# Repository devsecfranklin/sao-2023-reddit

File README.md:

# Shitty Add-On of Reddit avatar for DEFCON 2023

```sh
 ____  _____      _    ____    _  ___     ____ ____  
|  _ \| ____|_   / \  |  _ \ _/ |/ _ \ _ / ___| ___| 
| | | |  _| (_) / _ \ | | | (_) | | | (_) |   |___ \ 
| |_| | |___ _ / ___ \| |_| |_| | |_| |_| |___ ___) |
|____/|_____(_)_/   \_\____/(_)_|\___/(_)\____|____/ 
                                                     
```

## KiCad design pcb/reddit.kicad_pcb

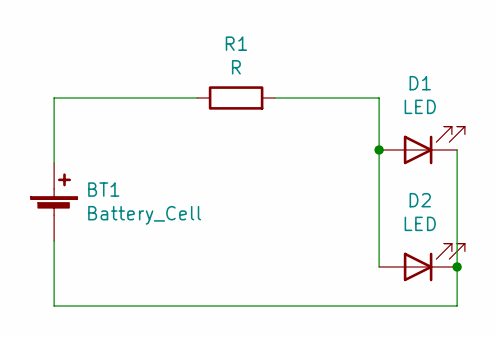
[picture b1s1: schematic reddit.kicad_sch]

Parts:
BT1: Battery_Cell; BatteryHolder_Keystone_3002_1x2032
D1, D2: LED; LED_PLCC-2_Reverse-Mount
R1: R; R_0805_2012Metric_Pad1.20x1.40mm_HandSolder

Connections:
unnamed: BT1.1 (+), R1.1
unnamed: BT1.2 (-), D1.1 (K), D2.1 (K)
unnamed: D1.2 (A), D2.2 (A), R1.2

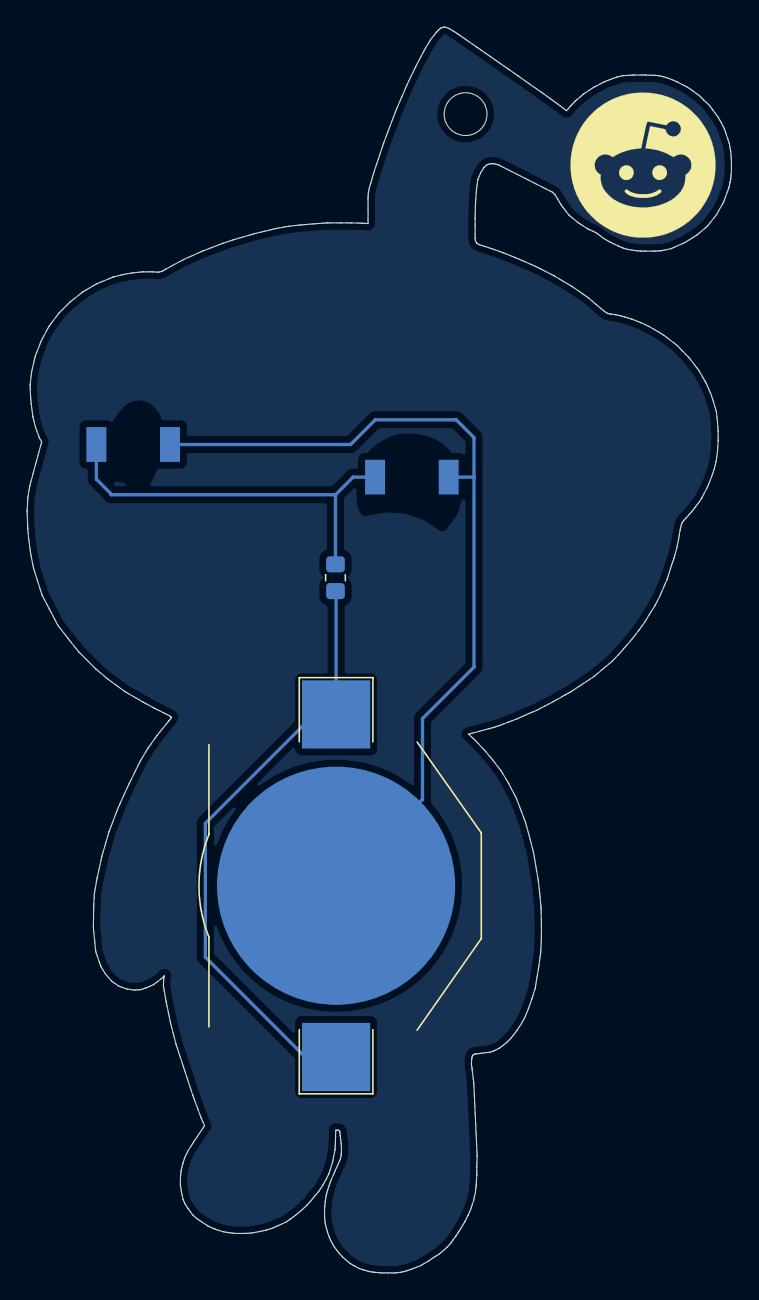
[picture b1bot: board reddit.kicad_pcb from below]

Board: 2 copper layers, 52.6 x 93.1 mm, 4 parts (4 on the bottom side), 3 nets.

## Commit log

2022-08-19 adding initial stuff
2022-08-20 schematic and components
2022-08-20 revision 1.0
2022-08-20 version 1.1
2022-08-20 version 1.2
2022-08-20 version 1.3
2022-08-21 version 1.4
2022-08-21 version 1.41
2022-08-23 version 1.5
2022-08-23 testing
2022-08-23 tune the GH action
2022-08-23 install pandoc
2022-08-24 tweak README
2022-08-24 tweak README (#4)
2022-08-24 Add renovate.json
2022-08-24 Add .whitesource configuration file
2022-08-24 Add renovate.json (#5)
2022-08-24 Update actions/checkout action to v3
2022-08-24 Update actions/upload-artifact action to v3
2022-08-24 Add .whitesource configuration file (#6)
2022-08-24 Update actions/checkout action to v3 (#8)
2022-08-24 Update actions/upload-artifact action to v3 (#9)
2022-08-25 Upgrading to KiCad 6
2022-08-25 udpate the board files
2022-08-25 remove old files
2022-08-25 P0lr1 (#11)
    * version 1.2
    * version 1.3
    * version 1.3
    * version 1.4
    * version 1.41
    * version 1.5
2023-05-22 updates from p0lr
2023-10-19 Update actions/checkout action to v4
2023-12-14 Update actions/upload-artifact action to v4
2024-05-24 Update actions/checkout action to v4 (#13)
2024-05-24 update README.md (#16)
2024-05-24 updates from p0lr (#12)
